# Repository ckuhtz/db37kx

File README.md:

3/13/2023: found a defect in this design, revising.

--

# An adapter board for Elecraft KX2/ KX3 to connect to microHAM micro KEYER III DB37 with standard 3.5mm TRS and TRRS cables.

See [blog post](https://holdmybeer.io/2023/02/28/micro-keyer-iii-elecraft-kx2-kx3-making-an-adapter-board/) for more detail. 

KiCad 7.0 files in this repo are licensed under [CC BY-SA 4.0](LICENSE.md). Use at your own risk.

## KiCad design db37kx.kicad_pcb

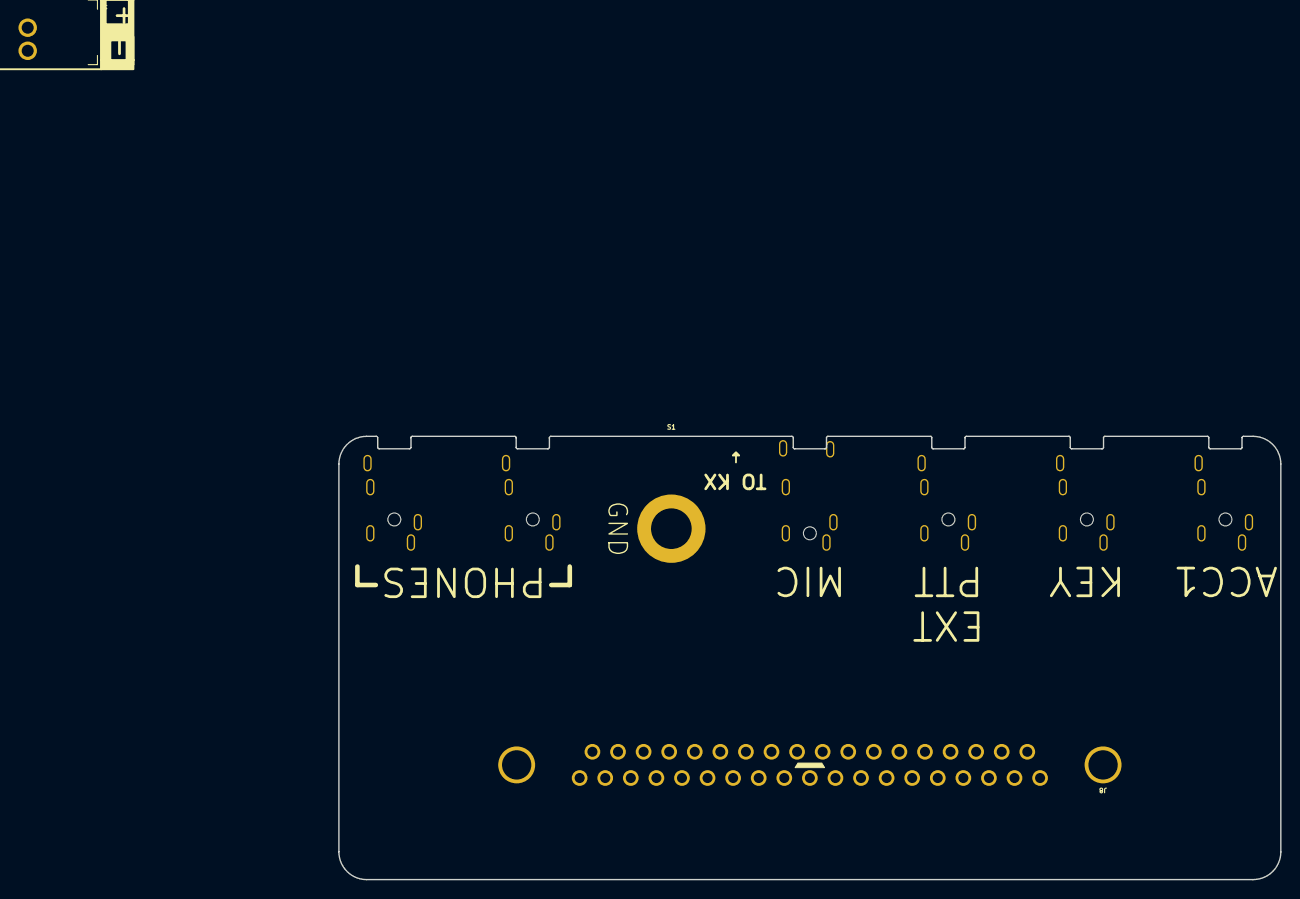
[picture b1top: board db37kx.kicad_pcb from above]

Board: 2 copper layers, 102.0 x 48.0 mm, 9 parts (0 on the bottom side), 17 nets.

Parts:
J1: 1989748
J2, J3, J5, J6, J7: 54-00299
J4: 54-00176
J8: K85X-CD-37S
S1: 9774030360R

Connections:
+12V: J1.1, J8.1
/CW OUT: J3.3 (T), J8.28
/FIF IN: J8.22, J8.23
/FILTER IN: J2.2 (R), J8.8
/FSW IN: J7.3 (T), J8.11, J8.12
/MIC: J8.16, J8.30
/MIC GND: J8.13, J8.34
/PTT: J4.3 (R1), J8.9, J8.27
/RADIO AF OUT: J5.3 (T), J6.3 (T), J8.19
/RADIO AF OUT GND: J5.1 (S), J6.1 (S), J8.37
/RADIO MIC IN: J4.4 (T), J8.17
/RADIO MIC IN GND: J4.1 (S), J8.35
/RADIO_R_PASSTHRU: J5.2 (R), J6.2 (R)
/RS232 OUT: J2.3 (T), J8.25
/RS232CTS: J8.2, J8.20
/RS-TTL OUT: J8.4, J8.5
GND: J1.2, J2.1 (S), J3.1 (S), J4.2 (R2), J7.1 (S), J7.2 (R), J8.31, J8.SH, S1.1

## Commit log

2023-02-27 fixed path ref
2023-03-12 updated .gitignore to include *.zip for all sorts of archives that are just noise.
2023-03-12 added board dimensions
2023-03-13 rev B start

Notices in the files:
db37kx.kicad_pcb:
Copyright © 2023 Christian Kuhtz
